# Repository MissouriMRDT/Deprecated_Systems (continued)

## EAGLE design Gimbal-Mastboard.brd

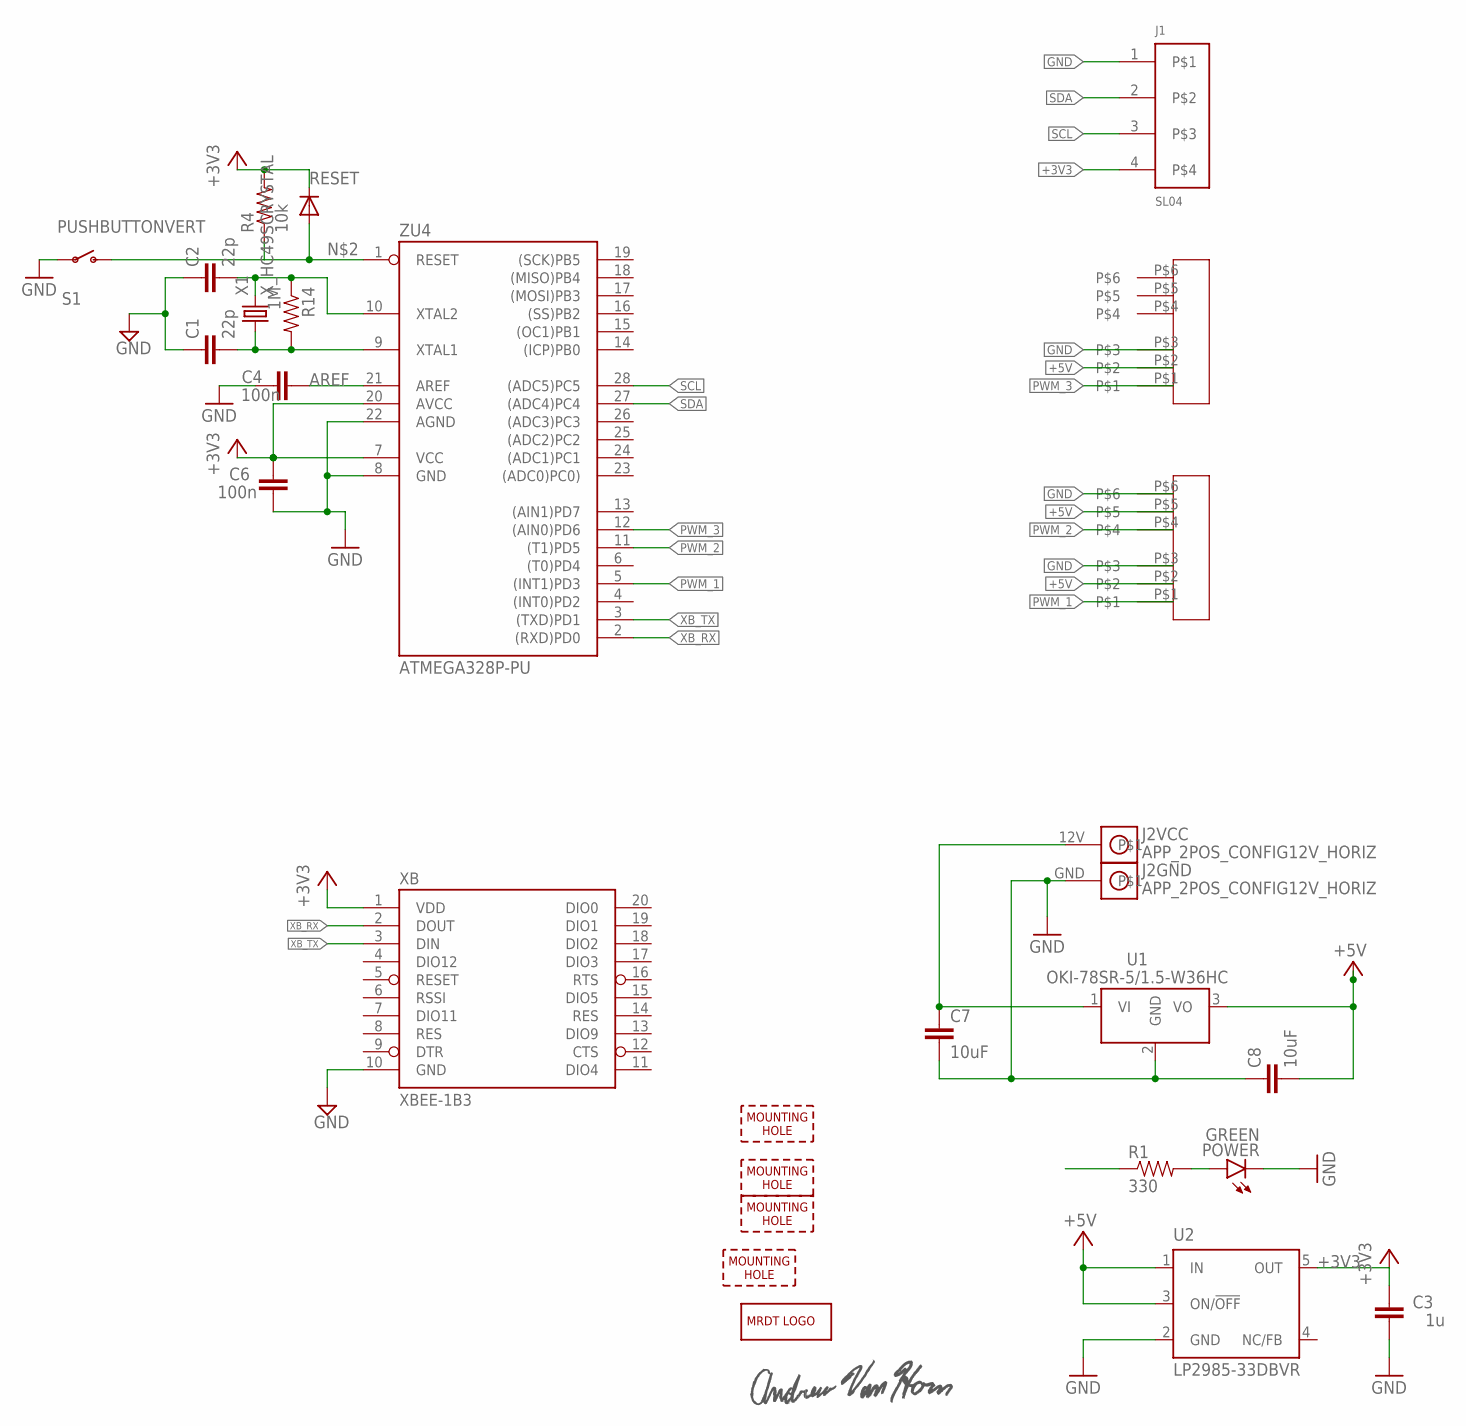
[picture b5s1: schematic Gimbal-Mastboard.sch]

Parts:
C1, C2: 22p; 0603-CAP
C3: 1u; C0603-ROUND
C4, C6: 100n; C0603-ROUND
C7, C8: 10uF; 0805
H1, H2, H3, H4: MOUNTING_HOLE#4; #4_SCREW
J1: SL04; MOLEX_SL_04_TH
J2: APP_2POS_CONFIG12V_HORIZ; APP45_12V_HORIZ_CONFIG
LOGO1: MRDT_LOGO
POWER: GREEN; LED-1206
R1: 330; 0805
R4: 10k; 0805
R14: 1M; 0603-RES
RESET: CD1206-S01575; MINIMELF
S1: PUSHBUTTONVERT; APEM-MJTP1243
U1: OKI-78SR-5/1.5-W36HC; OKI-78SR_HORIZ
U2: LP2985-33DBVR; SOT23-DBV
U$1, U$2: 2X3_BOX_HEADER_FEMALE
U$3: ANDREW_VAN_HORN_SIGNATURE
X1: X_HC49SCRYSTAL; HC-49
XB: XBEE-1B3; XBEE-SMD
ZU4: ATMEGA328P-PU; DIL28-3

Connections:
12V: C7.1, J2.12V, U1.1 (VI)
+3V3: C3.2, C6.2, J1.4, R1.1, R4.2, RESET.C, U2.5 (OUT), XB.1 (VDD), ZU4.7 (VCC), ZU4.20 (AVCC)
+5V: C8.2, U1.3 (VO), U2.1 (IN), U2.3 (ON/!OFF), U$1.P$2, U$2.P$2, U$2.P$5
AREF: C4.2, ZU4.21 (AREF)
GND: C1.1, C2.1, C3.1, C4.1, C6.1, C7.2, C8.1, J1.1, J2.GND, POWER.C, S1.P$1, U1.2 (GND), U2.2 (GND), U$1.P$3, U$2.P$3, U$2.P$6, XB.10 (GND), ZU4.8 (GND), ZU4.22 (AGND)
unnamed: C2.2, R14.1, X1.P$2 (2), ZU4.10 (XTAL2)
unnamed: R4.1, RESET.A, S1.P$2 (S), ZU4.1 (RESET)
unnamed: C1.2, R14.2, X1.P$1 (1), ZU4.9 (XTAL1)
unnamed: POWER.A, R1.2
PWM_1: U$2.P$1, ZU4.5 ((INT1)PD3)
PWM_2: U$2.P$4, ZU4.11 ((T1)PD5)
PWM_3: U$1.P$1, ZU4.12 ((AIN0)PD6)
SCL: J1.3, ZU4.28 ((ADC5)PC5)
SDA: J1.2, ZU4.27 ((ADC4)PC4)
XB_RX: XB.2 (DOUT), ZU4.2 ((RXD)PD0)
XB_TX: XB.3 (DIN), ZU4.3 ((TXD)PD1)

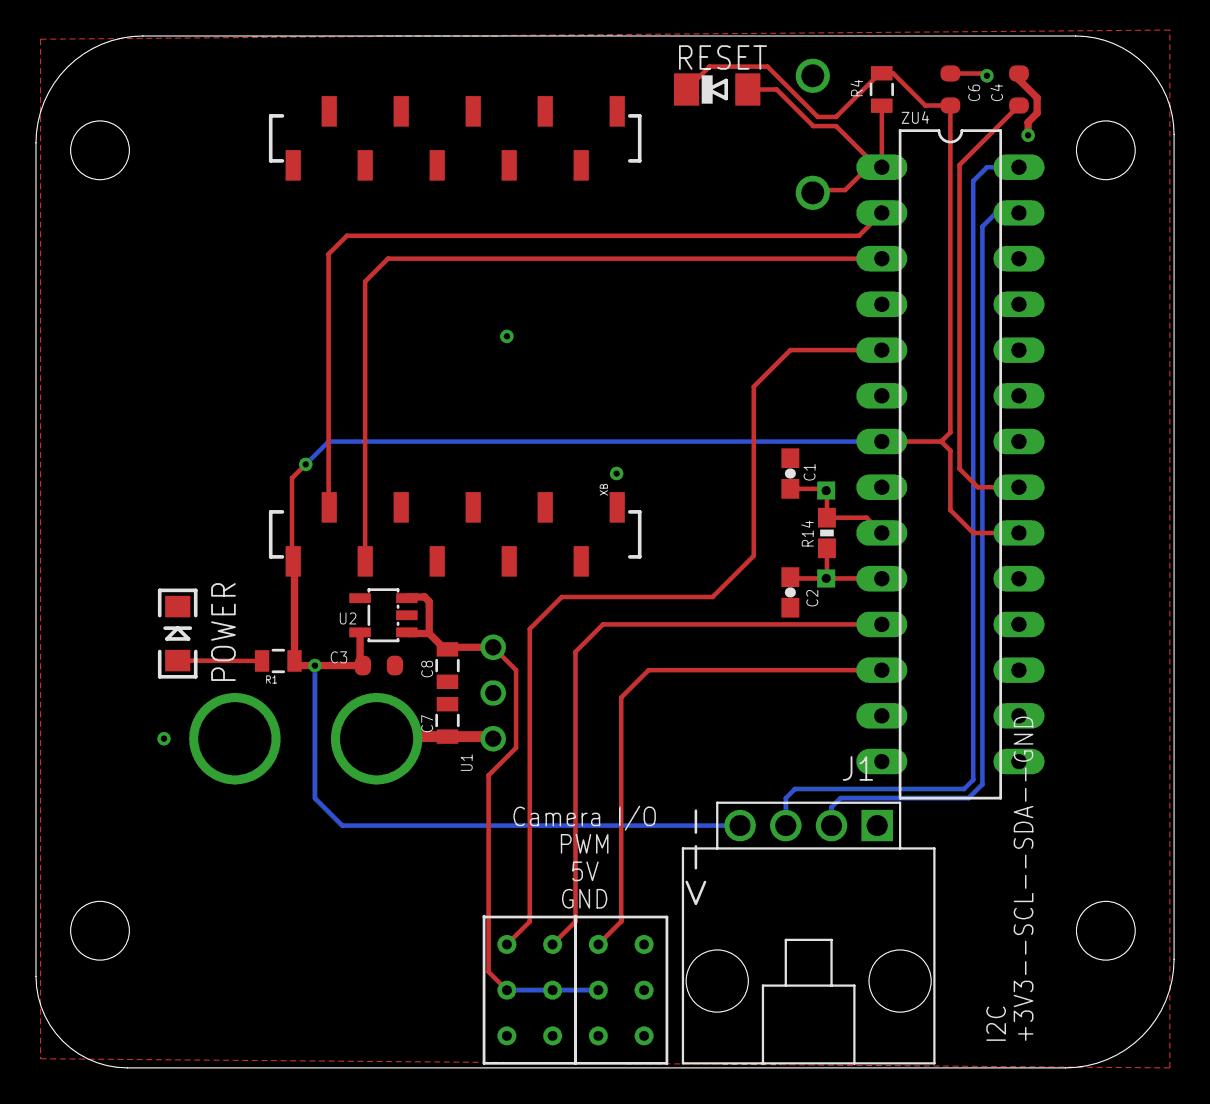
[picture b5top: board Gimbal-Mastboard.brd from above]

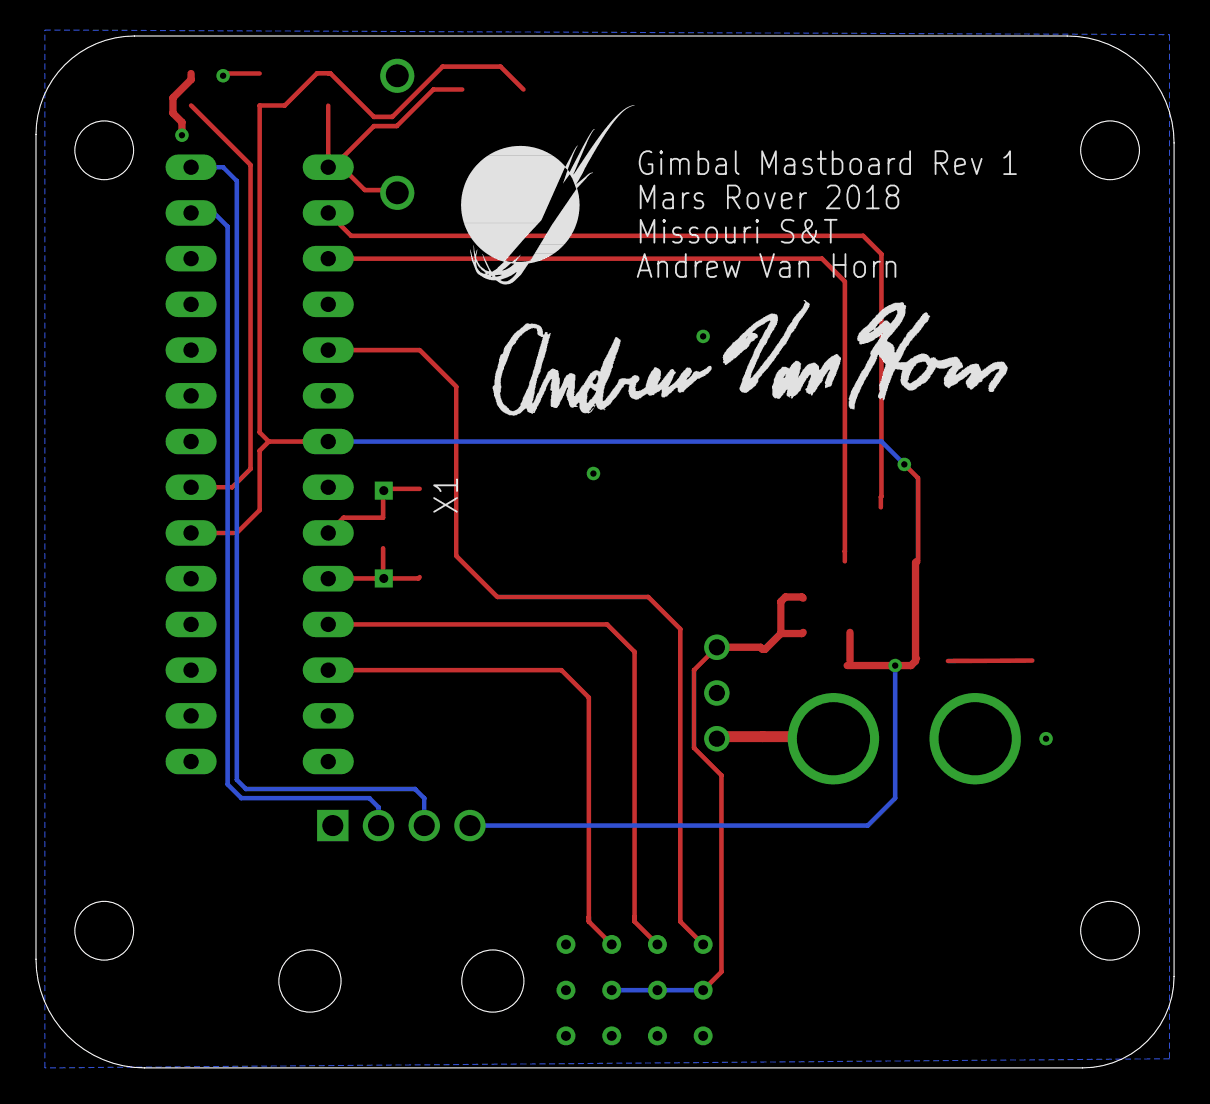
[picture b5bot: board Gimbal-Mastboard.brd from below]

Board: 2 copper layers, 63.2 x 57.3 mm, 28 parts (3 on the bottom side), 16 nets.

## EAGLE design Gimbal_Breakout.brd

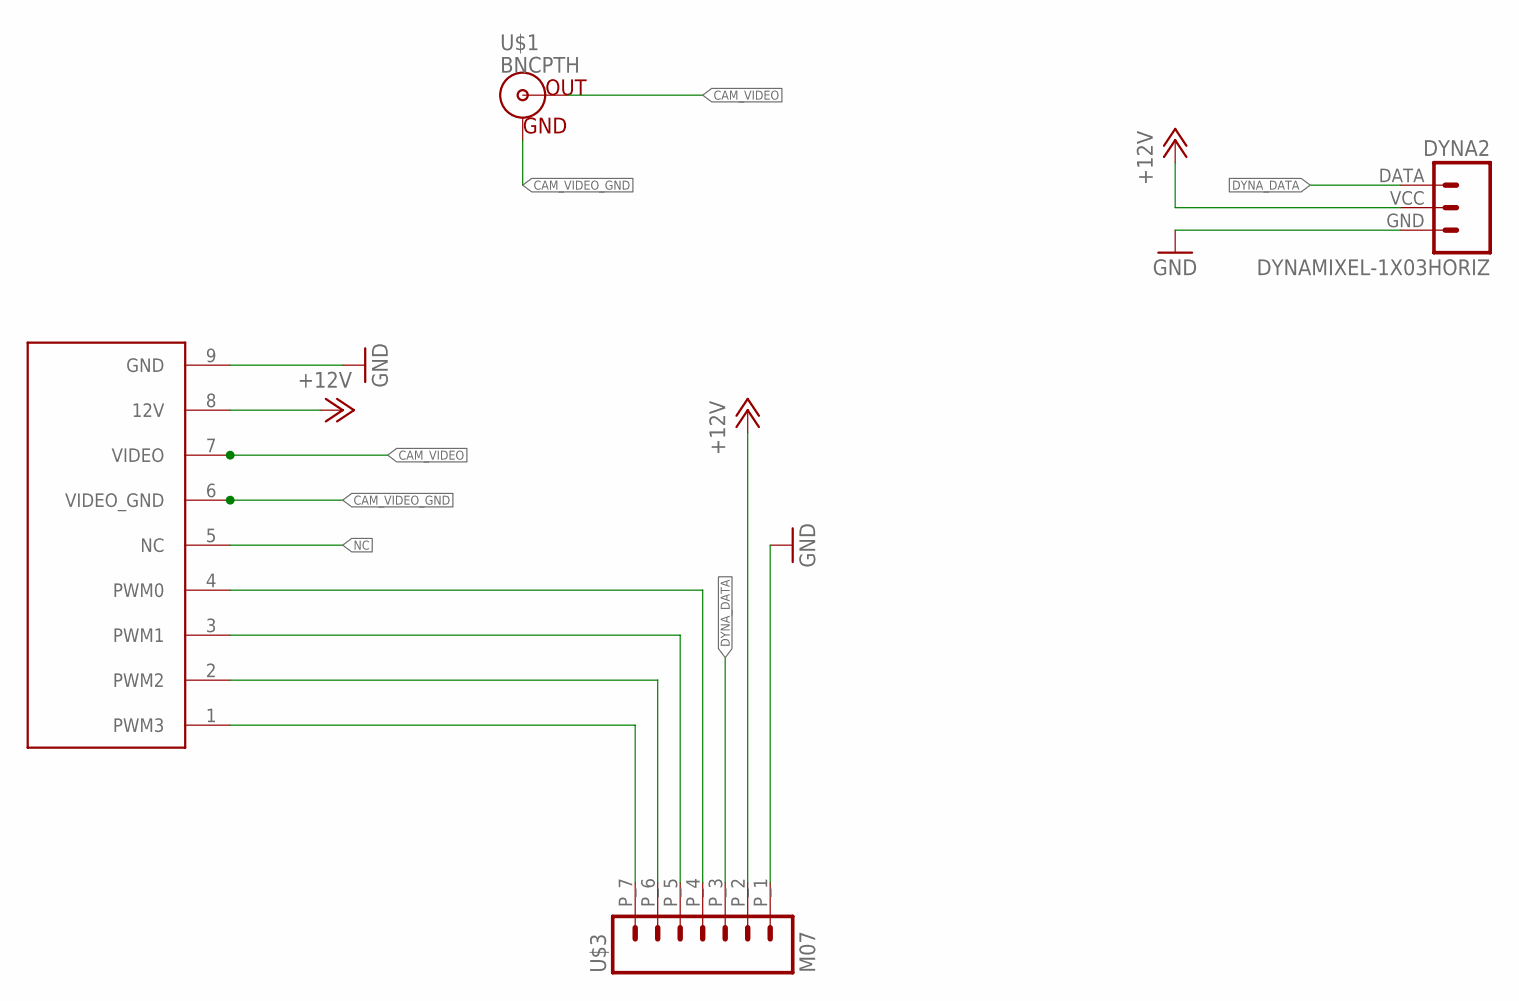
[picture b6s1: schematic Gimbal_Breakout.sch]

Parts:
DYNA2: DYNAMIXEL-1X03HORIZ; MLX-SPOX5268-3PIN
U$1: BNCPTH; BNC
U$3: M07; MOLEX_43650-07
U$4: CAMERA_BREAKOUT; CAM_CONNECTOR

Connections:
+12V: DYNA2.VCC, U$3.P_2 (2), U$4.8 (12V)
CAM_PWM0: U$3.P_4 (4), U$4.4 (PWM0)
CAM_PWM1: U$3.P_5 (5), U$4.3 (PWM1)
CAM_PWM2: U$3.P_6 (6), U$4.2 (PWM2)
CAM_PWM3: U$3.P_7 (7), U$4.1 (PWM3)
CAM_VIDEO: U$1.S (OUT), U$4.7 (VIDEO)
CAM_VIDEO_GND: U$1.GND, U$4.6 (VIDEO_GND)
DYNA_DATA: DYNA2.DATA, U$3.P_3 (3)
GND: DYNA2.GND, U$3.P_1 (1), U$4.9 (GND)

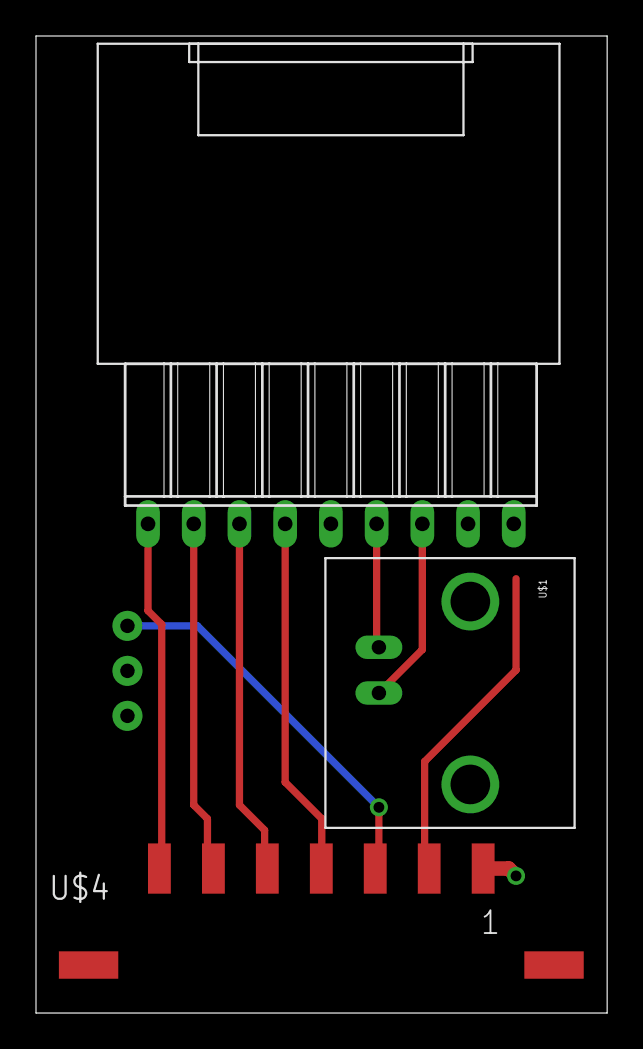
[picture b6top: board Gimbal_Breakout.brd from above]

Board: 2 copper layers, 31.7 x 54.3 mm, 4 parts (0 on the bottom side), 9 nets.

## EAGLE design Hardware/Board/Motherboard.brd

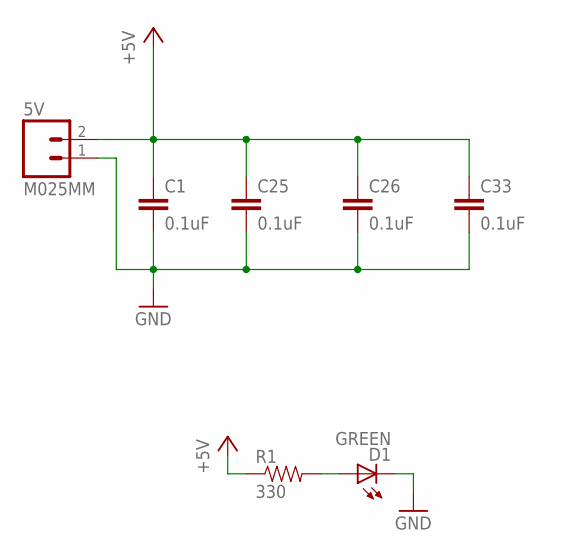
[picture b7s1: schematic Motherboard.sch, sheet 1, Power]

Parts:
5V: M025MM; SCREWTERMINAL-5MM-2
C1, C25, C26, C33: 0.1uF; 1206
D1: GREEN; LED-1206
R1: 330; 1206

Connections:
+5V: 5V.2, C1.1, C25.1, C26.1, C33.1, R1.1; also elsewhere on the board
GND: 5V.1, C1.2, C25.2, C26.2, C33.2, D1.C; also elsewhere on the board
unnamed: D1.A, R1.2

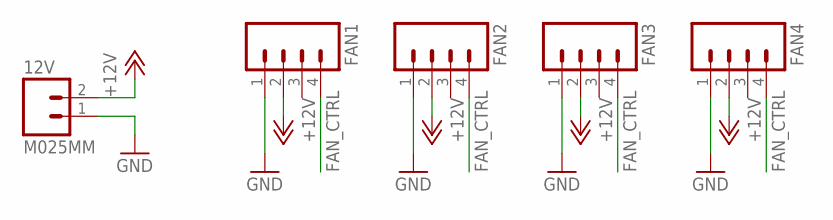
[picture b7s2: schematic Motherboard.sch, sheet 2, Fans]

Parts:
12V: M025MM; SCREWTERMINAL-5MM-2
FAN1, FAN2, FAN3, FAN4: M04LONGPADS; 1X04_LONGPADS

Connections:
+12V: 12V.2, FAN1.2, FAN2.2, FAN3.2, FAN4.2
FAN_CTRL: FAN1.4, FAN2.4, FAN3.4, FAN4.4; also elsewhere on the board
GND: 12V.1, FAN1.1, FAN2.1, FAN3.1, FAN4.1; also elsewhere on the board

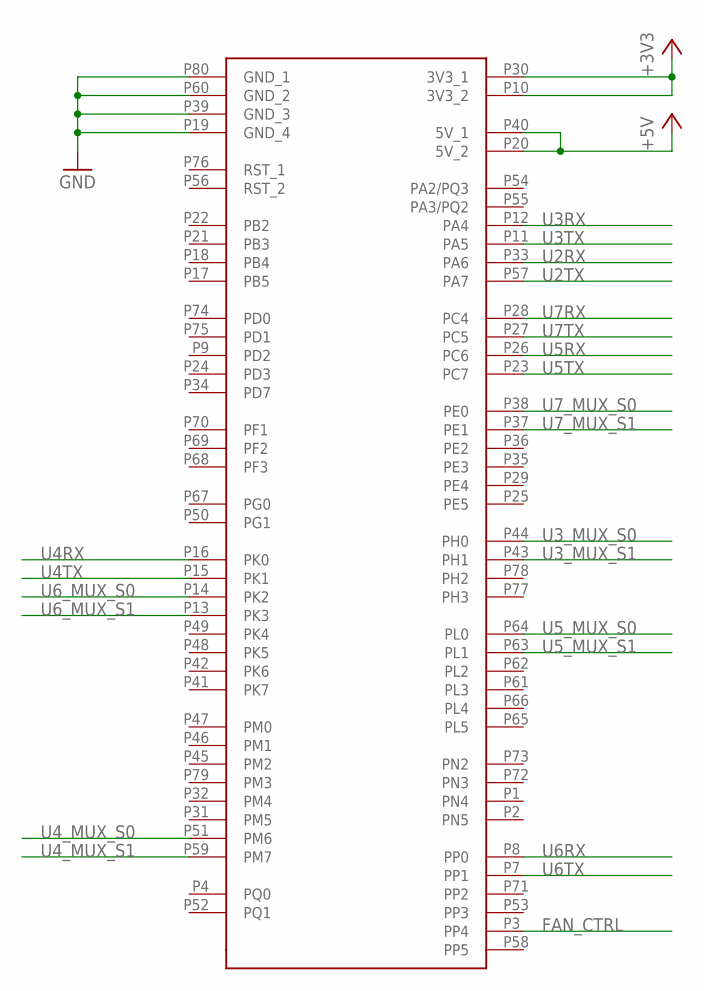
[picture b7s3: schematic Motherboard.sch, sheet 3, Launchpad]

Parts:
U$5: STELLARISLAUNCHPAD_CONNECTED

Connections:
+3V3: U$5.P10 (3V3_2), U$5.P30 (3V3_1); also elsewhere on the board
+5V: U$5.P20 (5V_2), U$5.P40 (5V_1); also elsewhere on the board
FAN_CTRL: U$5.P3 (PP4); also elsewhere on the board
GND: U$5.P19 (GND_4), U$5.P39 (GND_3), U$5.P60 (GND_2), U$5.P80 (GND_1); also elsewhere on the board
U2RX: U$5.P33 (PA6); also elsewhere on the board
U2TX: U$5.P57 (PA7); also elsewhere on the board
U3RX: U$5.P12 (PA4); also elsewhere on the board
U3TX: U$5.P11 (PA5); also elsewhere on the board
U3_MUX_S0: U$5.P44 (PH0); also elsewhere on the board
U3_MUX_S1: U$5.P43 (PH1); also elsewhere on the board
U4RX: U$5.P16 (PK0); also elsewhere on the board
U4TX: U$5.P15 (PK1); also elsewhere on the board
U4_MUX_S0: U$5.P51 (PM6); also elsewhere on the board
U4_MUX_S1: U$5.P59 (PM7); also elsewhere on the board
U5RX: U$5.P26 (PC6); also elsewhere on the board
U5TX: U$5.P23 (PC7); also elsewhere on the board
U5_MUX_S0: U$5.P64 (PL0); also elsewhere on the board
U5_MUX_S1: U$5.P63 (PL1); also elsewhere on the board
U6RX: U$5.P8 (PP0); also elsewhere on the board
U6TX: U$5.P7 (PP1); also elsewhere on the board
U6_MUX_S0: U$5.P14 (PK2); also elsewhere on the board
U6_MUX_S1: U$5.P13 (PK3); also elsewhere on the board
U7RX: U$5.P28 (PC4); also elsewhere on the board
U7TX: U$5.P27 (PC5); also elsewhere on the board
U7_MUX_S0: U$5.P38 (PE0); also elsewhere on the board
U7_MUX_S1: U$5.P37 (PE1); also elsewhere on the board

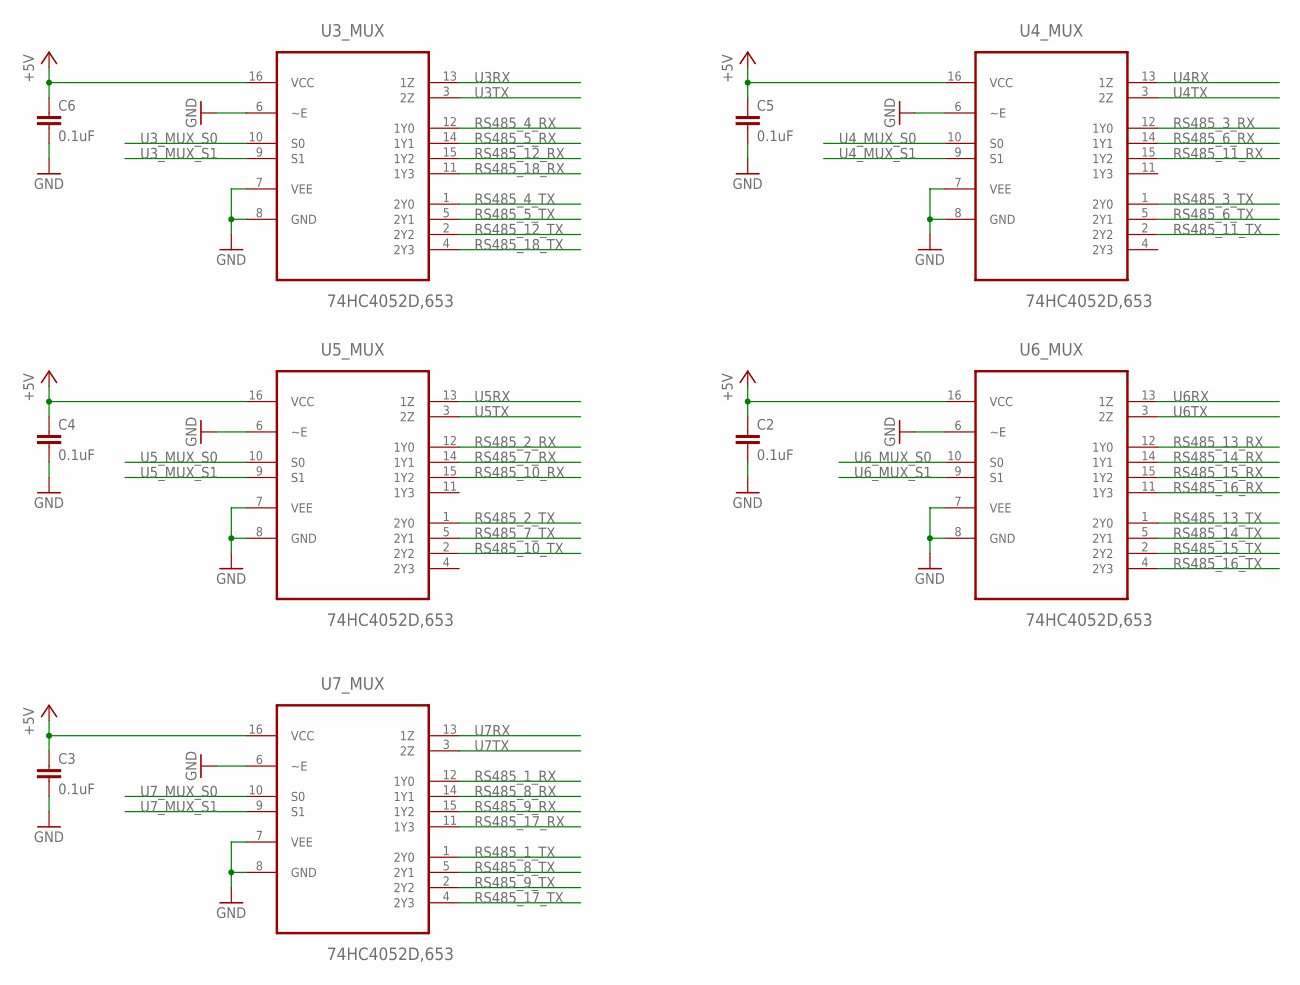
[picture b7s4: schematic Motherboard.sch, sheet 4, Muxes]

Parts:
C2, C3, C4, C5, C6: 0.1uF; 1206
U3_MUX, U4_MUX, U5_MUX, U6_MUX, U7_MUX: 74HC4052D,653; SOIC127P600X175-16N

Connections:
+5V: C2.1, C3.1, C4.1, C5.1, C6.1, U3_MUX.16 (VCC), U4_MUX.16 (VCC), U5_MUX.16 (VCC), U6_MUX.16 (VCC), U7_MUX.16 (VCC); also elsewhere on the board
GND: C2.2, C3.2, C4.2, C5.2, C6.2, U3_MUX.6 (~E), U3_MUX.7 (VEE), U3_MUX.8 (GND), U4_MUX.6 (~E), U4_MUX.7 (VEE), U4_MUX.8 (GND), U5_MUX.6 (~E), U5_MUX.7 (VEE), U5_MUX.8 (GND), U6_MUX.6 (~E), U6_MUX.7 (VEE), U6_MUX.8 (GND), U7_MUX.6 (~E), U7_MUX.7 (VEE), U7_MUX.8 (GND); also elsewhere on the board
RS485_1_RX: U7_MUX.12 (1Y0); also elsewhere on the board
RS485_1_TX: U7_MUX.1 (2Y0); also elsewhere on the board
RS485_2_RX: U5_MUX.12 (1Y0); also elsewhere on the board
RS485_2_TX: U5_MUX.1 (2Y0); also elsewhere on the board
RS485_3_RX: U4_MUX.12 (1Y0); also elsewhere on the board
RS485_3_TX: U4_MUX.1 (2Y0); also elsewhere on the board
RS485_4_RX: U3_MUX.12 (1Y0); also elsewhere on the board
RS485_4_TX: U3_MUX.1 (2Y0); also elsewhere on the board
RS485_5_RX: U3_MUX.14 (1Y1); also elsewhere on the board
RS485_5_TX: U3_MUX.5 (2Y1); also elsewhere on the board
RS485_6_RX: U4_MUX.14 (1Y1); also elsewhere on the board
RS485_6_TX: U4_MUX.5 (2Y1); also elsewhere on the board
RS485_7_RX: U5_MUX.14 (1Y1); also elsewhere on the board
RS485_7_TX: U5_MUX.5 (2Y1); also elsewhere on the board
RS485_8_RX: U7_MUX.14 (1Y1); also elsewhere on the board
RS485_8_TX: U7_MUX.5 (2Y1); also elsewhere on the board
RS485_9_RX: U7_MUX.15 (1Y2); also elsewhere on the board
RS485_9_TX: U7_MUX.2 (2Y2); also elsewhere on the board
RS485_10_RX: U5_MUX.15 (1Y2); also elsewhere on the board
RS485_10_TX: U5_MUX.2 (2Y2); also elsewhere on the board
RS485_11_RX: U4_MUX.15 (1Y2); also elsewhere on the board
RS485_11_TX: U4_MUX.2 (2Y2); also elsewhere on the board
RS485_12_RX: U3_MUX.15 (1Y2); also elsewhere on the board
RS485_12_TX: U3_MUX.2 (2Y2); also elsewhere on the board
RS485_13_RX: U6_MUX.12 (1Y0); also elsewhere on the board
RS485_13_TX: U6_MUX.1 (2Y0); also elsewhere on the board
RS485_14_RX: U6_MUX.14 (1Y1); also elsewhere on the board
RS485_14_TX: U6_MUX.5 (2Y1); also elsewhere on the board
RS485_15_RX: U6_MUX.15 (1Y2); also elsewhere on the board
RS485_15_TX: U6_MUX.2 (2Y2); also elsewhere on the board
RS485_16_RX: U6_MUX.11 (1Y3); also elsewhere on the board
RS485_16_TX: U6_MUX.4 (2Y3); also elsewhere on the board
RS485_17_RX: U7_MUX.11 (1Y3); also elsewhere on the board
RS485_17_TX: U7_MUX.4 (2Y3); also elsewhere on the board
RS485_18_RX: U3_MUX.11 (1Y3); also elsewhere on the board
RS485_18_TX: U3_MUX.4 (2Y3); also elsewhere on the board
U3RX: U3_MUX.13 (1Z); also elsewhere on the board
U3TX: U3_MUX.3 (2Z); also elsewhere on the board
U3_MUX_S0: U3_MUX.10 (S0); also elsewhere on the board
U3_MUX_S1: U3_MUX.9 (S1); also elsewhere on the board
U4RX: U4_MUX.13 (1Z); also elsewhere on the board
U4TX: U4_MUX.3 (2Z); also elsewhere on the board
U4_MUX_S0: U4_MUX.10 (S0); also elsewhere on the board
U4_MUX_S1: U4_MUX.9 (S1); also elsewhere on the board
U5RX: U5_MUX.13 (1Z); also elsewhere on the board
U5TX: U5_MUX.3 (2Z); also elsewhere on the board
U5_MUX_S0: U5_MUX.10 (S0); also elsewhere on the board
U5_MUX_S1: U5_MUX.9 (S1); also elsewhere on the board
U6RX: U6_MUX.13 (1Z); also elsewhere on the board
U6TX: U6_MUX.3 (2Z); also elsewhere on the board
U6_MUX_S0: U6_MUX.10 (S0); also elsewhere on the board
U6_MUX_S1: U6_MUX.9 (S1); also elsewhere on the board
U7RX: U7_MUX.13 (1Z); also elsewhere on the board
U7TX: U7_MUX.3 (2Z); also elsewhere on the board
U7_MUX_S0: U7_MUX.10 (S0); also elsewhere on the board
U7_MUX_S1: U7_MUX.9 (S1); also elsewhere on the board

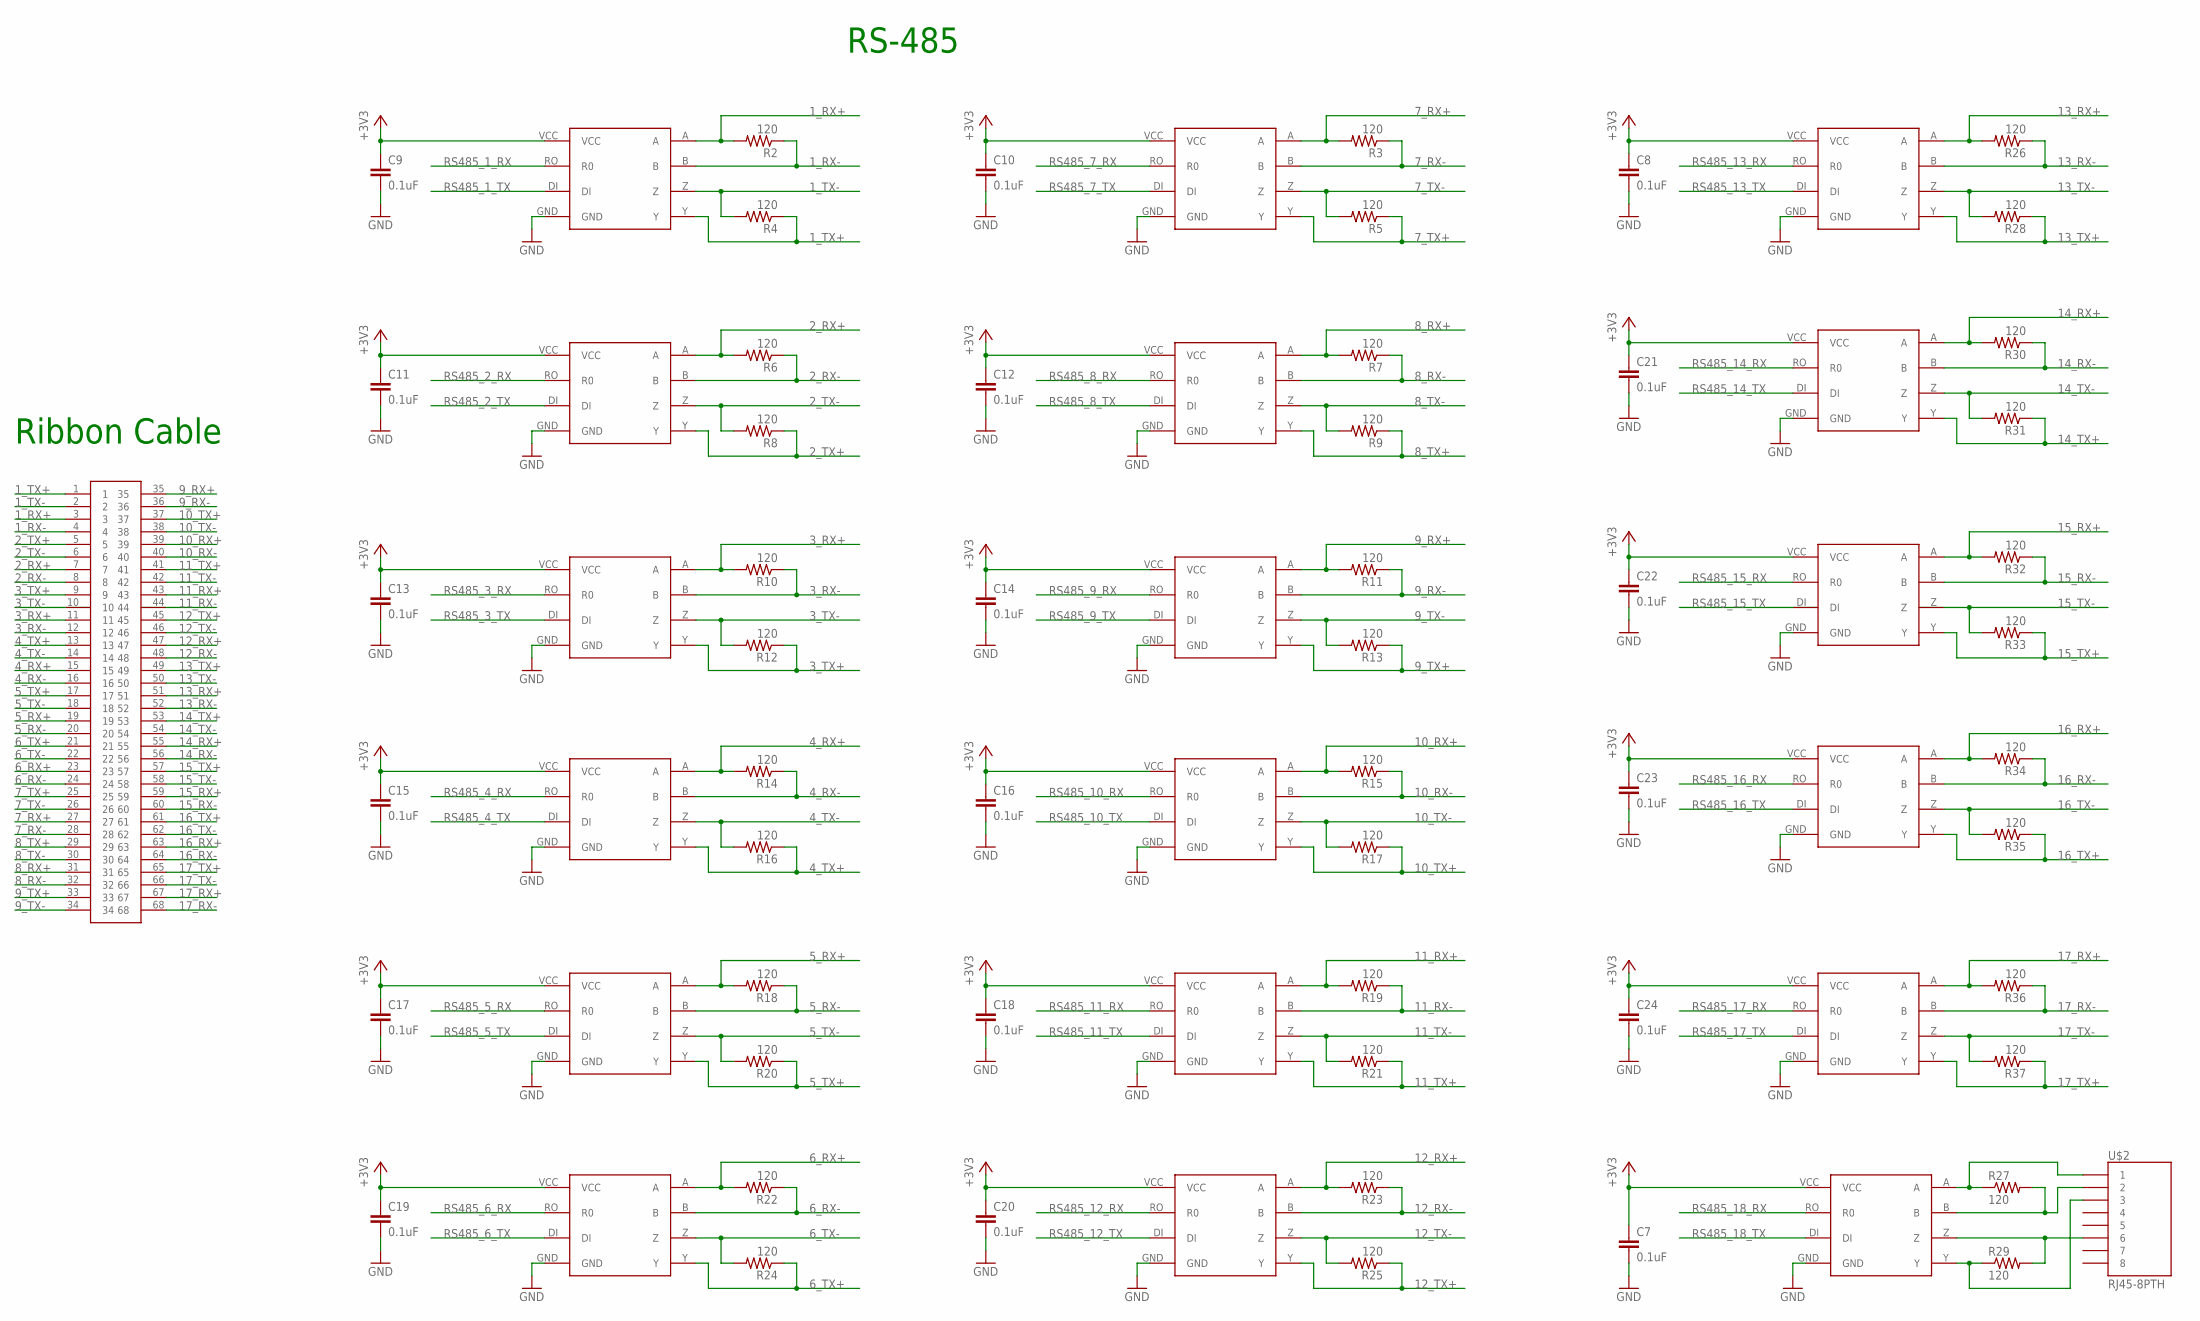
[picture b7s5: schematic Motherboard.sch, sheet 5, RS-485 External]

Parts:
C7, C8, C9, C10, C11, C12, C13, C14, C15, C16, C17, C18, C19, C20, C21, C22, C23, C24: 0.1uF; 1206
R2, R3, R4, R5, R6, R7, R8, R9, R10, R11, R12, R13, R14, R15, R16, R17, R18, R19, R20, R21, R22, R23, R24, R25, R26, R27, R28, R29, R30, R31, R32, R33, R34, R35, R36, R37: 120; 1206
RS-485-2: MAX3077; MAX3070E
RS_TRANS_1, RS_TRANS_2, RS_TRANS_3, RS_TRANS_4, RS_TRANS_5, RS_TRANS_6, RS_TRANS_7, RS_TRANS_8, RS_TRANS_9, RS_TRANS_10, RS_TRANS_11, RS_TRANS_12, RS_TRANS_13, RS_TRANS_14, RS_TRANS_15, RS_TRANS_16, RS_TRANS_17: MAX3077; MAX3070E
U$2: RJ45-8PTH; RJ45-8
U$4: TB60050685100; 60050685100

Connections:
1_RX+: R2.2, RS_TRANS_1.A, U$4.3
1_RX-: R2.1, RS_TRANS_1.B, U$4.4
1_TX+: R4.1, RS_TRANS_1.Y, U$4.1
1_TX-: R4.2, RS_TRANS_1.Z, U$4.2
2_RX+: R6.2, RS_TRANS_3.A, U$4.7
2_RX-: R6.1, RS_TRANS_3.B, U$4.8
2_TX+: R8.1, RS_TRANS_3.Y, U$4.5
2_TX-: R8.2, RS_TRANS_3.Z, U$4.6
3_RX+: R10.2, RS_TRANS_5.A, U$4.11
3_RX-: R10.1, RS_TRANS_5.B, U$4.12
3_TX+: R12.1, RS_TRANS_5.Y, U$4.9
3_TX-: R12.2, RS_TRANS_5.Z, U$4.10
4_RX+: R14.2, RS_TRANS_7.A, U$4.15
4_RX-: R14.1, RS_TRANS_7.B, U$4.16
4_TX+: R16.1, RS_TRANS_7.Y, U$4.13
4_TX-: R16.2, RS_TRANS_7.Z, U$4.14
5_RX+: R18.2, RS_TRANS_9.A, U$4.19
5_RX-: R18.1, RS_TRANS_9.B, U$4.20
5_TX+: R20.1, RS_TRANS_9.Y, U$4.17
5_TX-: R20.2, RS_TRANS_9.Z, U$4.18
6_RX+: R22.2, RS_TRANS_11.A, U$4.23
6_RX-: R22.1, RS_TRANS_11.B, U$4.24
6_TX+: R24.1, RS_TRANS_11.Y, U$4.21
6_TX-: R24.2, RS_TRANS_11.Z, U$4.22
7_RX+: R3.2, RS_TRANS_2.A, U$4.27
7_RX-: R3.1, RS_TRANS_2.B, U$4.28
7_TX+: R5.1, RS_TRANS_2.Y, U$4.25
7_TX-: R5.2, RS_TRANS_2.Z, U$4.26
8_RX+: R7.2, RS_TRANS_4.A, U$4.31
8_RX-: R7.1, RS_TRANS_4.B, U$4.32
8_TX+: R9.1, RS_TRANS_4.Y, U$4.29
8_TX-: R9.2, RS_TRANS_4.Z, U$4.30
9_RX+: R11.2, RS_TRANS_6.A, U$4.35
9_RX-: R11.1, RS_TRANS_6.B, U$4.36
9_TX+: R13.1, RS_TRANS_6.Y, U$4.33
9_TX-: R13.2, RS_TRANS_6.Z, U$4.34
10_RX+: R15.2, RS_TRANS_8.A, U$4.39
10_RX-: R15.1, RS_TRANS_8.B, U$4.40
10_TX+: R17.1, RS_TRANS_8.Y, U$4.37
10_TX-: R17.2, RS_TRANS_8.Z, U$4.38
11_RX+: R19.2, RS_TRANS_10.A, U$4.43
11_RX-: R19.1, RS_TRANS_10.B, U$4.44
11_TX+: R21.1, RS_TRANS_10.Y, U$4.41
11_TX-: R21.2, RS_TRANS_10.Z, U$4.42
12_RX+: R23.2, RS_TRANS_12.A, U$4.47
12_RX-: R23.1, RS_TRANS_12.B, U$4.48
12_TX+: R25.1, RS_TRANS_12.Y, U$4.45
12_TX-: R25.2, RS_TRANS_12.Z, U$4.46
13_RX+: R26.2, RS_TRANS_13.A, U$4.51
13_RX-: R26.1, RS_TRANS_13.B, U$4.52
13_TX+: R28.1, RS_TRANS_13.Y, U$4.49
13_TX-: R28.2, RS_TRANS_13.Z, U$4.50
14_RX+: R30.2, RS_TRANS_14.A, U$4.55
14_RX-: R30.1, RS_TRANS_14.B, U$4.56
14_TX+: R31.1, RS_TRANS_14.Y, U$4.53
14_TX-: R31.2, RS_TRANS_14.Z, U$4.54
15_RX+: R32.2, RS_TRANS_15.A, U$4.59
15_RX-: R32.1, RS_TRANS_15.B, U$4.60
15_TX+: R33.1, RS_TRANS_15.Y, U$4.57
15_TX-: R33.2, RS_TRANS_15.Z, U$4.58
16_RX+: R34.2, RS_TRANS_16.A, U$4.63
16_RX-: R34.1, RS_TRANS_16.B, U$4.64
16_TX+: R35.1, RS_TRANS_16.Y, U$4.61
16_TX-: R35.2, RS_TRANS_16.Z, U$4.62
17_RX+: R36.2, RS_TRANS_17.A, U$4.67
17_RX-: R36.1, RS_TRANS_17.B, U$4.68
17_TX+: R37.1, RS_TRANS_17.Y, U$4.65
17_TX-: R37.2, RS_TRANS_17.Z, U$4.66
+3V3: C7.1, C8.1, C9.1, C10.1, C11.1, C12.1, C13.1, C14.1, C15.1, C16.1, C17.1, C18.1, C19.1, C20.1, C21.1, C22.1, C23.1, C24.1, RS-485-2.VCC, RS_TRANS_1.VCC, RS_TRANS_2.VCC, RS_TRANS_3.VCC, RS_TRANS_4.VCC, RS_TRANS_5.VCC, RS_TRANS_6.VCC, RS_TRANS_7.VCC, RS_TRANS_8.VCC, RS_TRANS_9.VCC, RS_TRANS_10.VCC, RS_TRANS_11.VCC, RS_TRANS_12.VCC, RS_TRANS_13.VCC, RS_TRANS_14.VCC, RS_TRANS_15.VCC, RS_TRANS_16.VCC, RS_TRANS_17.VCC; also elsewhere on the board
GND: C7.2, C8.2, C9.2, C10.2, C11.2, C12.2, C13.2, C14.2, C15.2, C16.2, C17.2, C18.2, C19.2, C20.2, C21.2, C22.2, C23.2, C24.2, RS-485-2.GND, RS_TRANS_1.GND, RS_TRANS_2.GND, RS_TRANS_3.GND, RS_TRANS_4.GND, RS_TRANS_5.GND, RS_TRANS_6.GND, RS_TRANS_7.GND, RS_TRANS_8.GND, RS_TRANS_9.GND, RS_TRANS_10.GND, RS_TRANS_11.GND, RS_TRANS_12.GND, RS_TRANS_13.GND, RS_TRANS_14.GND, RS_TRANS_15.GND, RS_TRANS_16.GND, RS_TRANS_17.GND; also elsewhere on the board
unnamed: R29.2, RS-485-2.Z, U$2.6
unnamed: R27.1, RS-485-2.A, U$2.1
unnamed: R27.2, RS-485-2.B, U$2.2
unnamed: R29.1, RS-485-2.Y, U$2.3
RS485_1_RX: RS_TRANS_1.RO (R0); also elsewhere on the board
RS485_1_TX: RS_TRANS_1.DI; also elsewhere on the board
RS485_2_RX: RS_TRANS_3.RO (R0); also elsewhere on the board
RS485_2_TX: RS_TRANS_3.DI; also elsewhere on the board
RS485_3_RX: RS_TRANS_5.RO (R0); also elsewhere on the board
RS485_3_TX: RS_TRANS_5.DI; also elsewhere on the board
RS485_4_RX: RS_TRANS_7.RO (R0); also elsewhere on the board
RS485_4_TX: RS_TRANS_7.DI; also elsewhere on the board
RS485_5_RX: RS_TRANS_9.RO (R0); also elsewhere on the board
RS485_5_TX: RS_TRANS_9.DI; also elsewhere on the board
RS485_6_RX: RS_TRANS_11.RO (R0); also elsewhere on the board
RS485_6_TX: RS_TRANS_11.DI; also elsewhere on the board
RS485_7_RX: RS_TRANS_2.RO (R0); also elsewhere on the board
RS485_7_TX: RS_TRANS_2.DI; also elsewhere on the board
RS485_8_RX: RS_TRANS_4.RO (R0); also elsewhere on the board
RS485_8_TX: RS_TRANS_4.DI; also elsewhere on the board
RS485_9_RX: RS_TRANS_6.RO (R0); also elsewhere on the board
RS485_9_TX: RS_TRANS_6.DI; also elsewhere on the board
RS485_10_RX: RS_TRANS_8.RO (R0); also elsewhere on the board
RS485_10_TX: RS_TRANS_8.DI; also elsewhere on the board
RS485_11_RX: RS_TRANS_10.RO (R0); also elsewhere on the board
RS485_11_TX: RS_TRANS_10.DI; also elsewhere on the board
RS485_12_RX: RS_TRANS_12.RO (R0); also elsewhere on the board
RS485_12_TX: RS_TRANS_12.DI; also elsewhere on the board
RS485_13_RX: RS_TRANS_13.RO (R0); also elsewhere on the board
RS485_13_TX: RS_TRANS_13.DI; also elsewhere on the board
RS485_14_RX: RS_TRANS_14.RO (R0); also elsewhere on the board
RS485_14_TX: RS_TRANS_14.DI; also elsewhere on the board
RS485_15_RX: RS_TRANS_15.RO (R0); also elsewhere on the board
RS485_15_TX: RS_TRANS_15.DI; also elsewhere on the board
RS485_16_RX: RS_TRANS_16.RO (R0); also elsewhere on the board
RS485_16_TX: RS_TRANS_16.DI; also elsewhere on the board
RS485_17_RX: RS_TRANS_17.RO (R0); also elsewhere on the board
RS485_17_TX: RS_TRANS_17.DI; also elsewhere on the board
RS485_18_RX: RS-485-2.RO (R0); also elsewhere on the board
RS485_18_TX: RS-485-2.DI; also elsewhere on the board

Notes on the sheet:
Ribbon Cable
RS-485

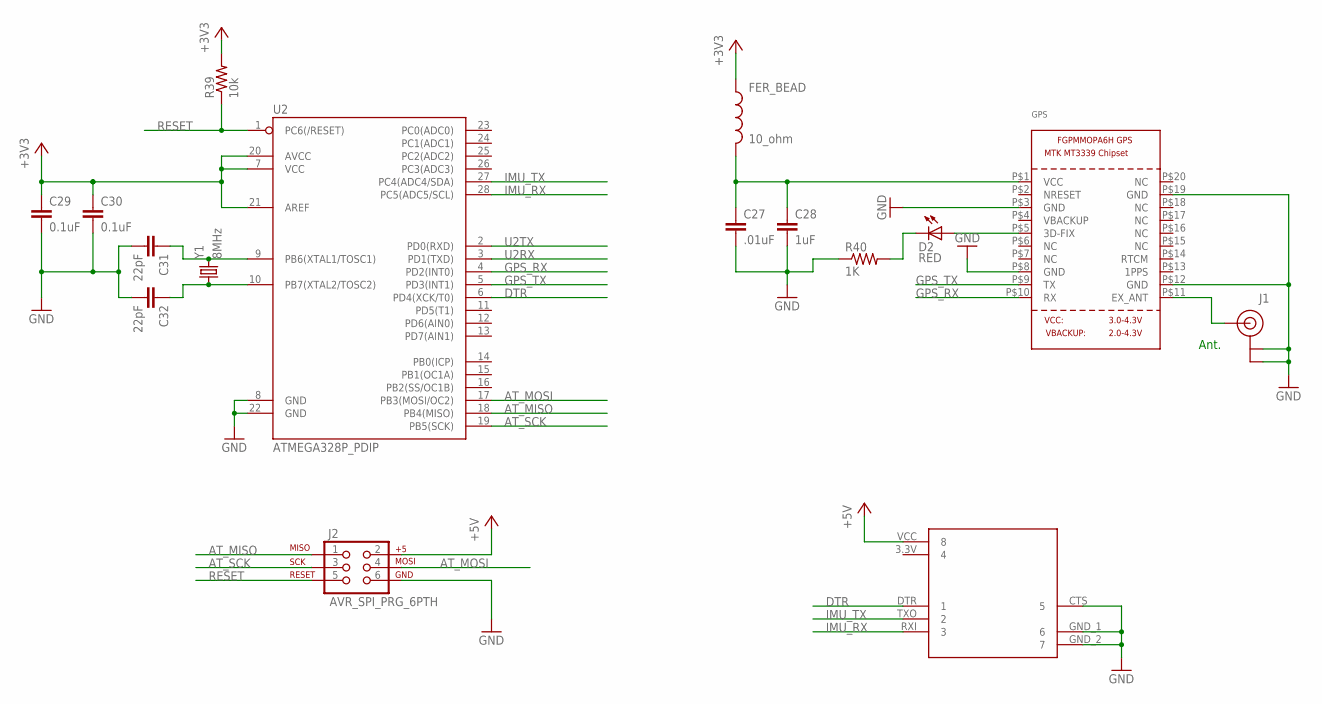
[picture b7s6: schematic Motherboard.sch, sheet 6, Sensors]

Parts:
C27: .01uF; 1206
C28: 1uF; 1206
C29, C30: 0.1uF; 1206
C31, C32: 22pF; 1206
D2: RED; LED-1206
FER_BEAD: 10_ohm; 0603
GPS: GPS_FGPMMOPA6H; FGPMMOPA6H
J1: U.FL
J2: AVR_SPI_PRG_6PTH; 2X3
R39: 10k; 1206
R40: 1K; 1206
U2: ATMEGA328P_PDIP; DIL28-3
U$1: RAZOR_IMU
Y1: 8MHz; HC49US

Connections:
+3V3: C29.1, C30.1, FER_BEAD.1, R39.2, U2.7 (VCC), U2.20 (AVCC), U2.21 (AREF); also elsewhere on the board
+5V: J2.2, U$1.VCC (8); also elsewhere on the board
ATCLK3: C32.1, U2.10 (PB7(XTAL2/TOSC2)), Y1.1
ATCLK4: C31.1, U2.9 (PB6(XTAL1/TOSC1)), Y1.2
AT_MISO: J2.1, U2.18 (PB4(MISO))
AT_MOSI: J2.4, U2.17 (PB3(MOSI/OC2))
AT_SCK: J2.3, U2.19 (PB5(SCK))
DTR: U2.6 (PD4(XCK/T0)), U$1.DTR (1)
GND: C27.2, C28.2, C29.2, C30.2, C31.2, C32.2, GPS.P$3 (GND), GPS.P$8 (GND), GPS.P$12 (GND), GPS.P$19 (GND), J1.P$1 (GND), J1.P$2 (GND), J2.6, R40.1, U2.8 (GND), U2.22 (GND), U$1.CTS (5), U$1.GND_1 (6), U$1.GND_2 (7); also elsewhere on the board
GPS_RX: GPS.P$10 (RX), U2.4 (PD2(INT0))
GPS_TX: GPS.P$9 (TX), U2.5 (PD3(INT1))
IMU_RX: U2.28 (PC5(ADC5/SCL)), U$1.RXI (3)
IMU_TX: U2.27 (PC4(ADC4/SDA)), U$1.TXO (2)
unnamed: GPS.P$11 (EX_ANT), J1.P$3 (SIGNAL)
unnamed: D2.C, R40.2
unnamed: D2.A, GPS.P$5 (3D-FIX)
unnamed: C27.1, C28.1, FER_BEAD.2, GPS.P$1 (VCC)
RESET: J2.5, R39.1, U2.1 (PC6(/RESET))
U2RX: U2.3 (PD1(TXD)); also elsewhere on the board
U2TX: U2.2 (PD0(RXD)); also elsewhere on the board

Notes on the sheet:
Ant.
